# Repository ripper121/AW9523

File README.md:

# AW9523 is a 16 I/O Port-Expander
#### What is it?
AW9523 is a 16 I/O Port-Expander. Very cheap and easy to use with Arduino.

Arduino Library: [Github](https://github.com/adafruit/Adafruit_AW9523)

#### Why did you make it?
I looked for a cheap and small port Expander and found that part on LCSC, so I created this PCB.

#### What makes it special?
AW9523 Features:

- 16 multi-function I/O, each for LED drive (current-source dimming) or GPIO mode
- 256 steps linear dimming in LED drive mode
- Any GPIO can be configured as an input or an output independently
- Support interrupt, 8us deglitch, low-level active
- Standard I2C interface, A1/A0 select I2C device address
- SDA, SCL, SHDN, and all GPIO can accept in 1.8V logic input
- ESD protection: ±4000V HBM (MIL-STD-883H Method 3015.8 standard）
- Latch-up ：±450mA（ JEDEC STANDARD NO.78C SEPTEMBER 2010 standard）
- Supply shutdown function, low-level active
- 2.5V~5.5V power supply
- I2C address default 0x58 (can be 0x59, 0x5A or 0x5B)

You can buy this board form my Tindie Store: https://www.tindie.com/products/ripper121/aw9523-breakout-16-io-port-expander/

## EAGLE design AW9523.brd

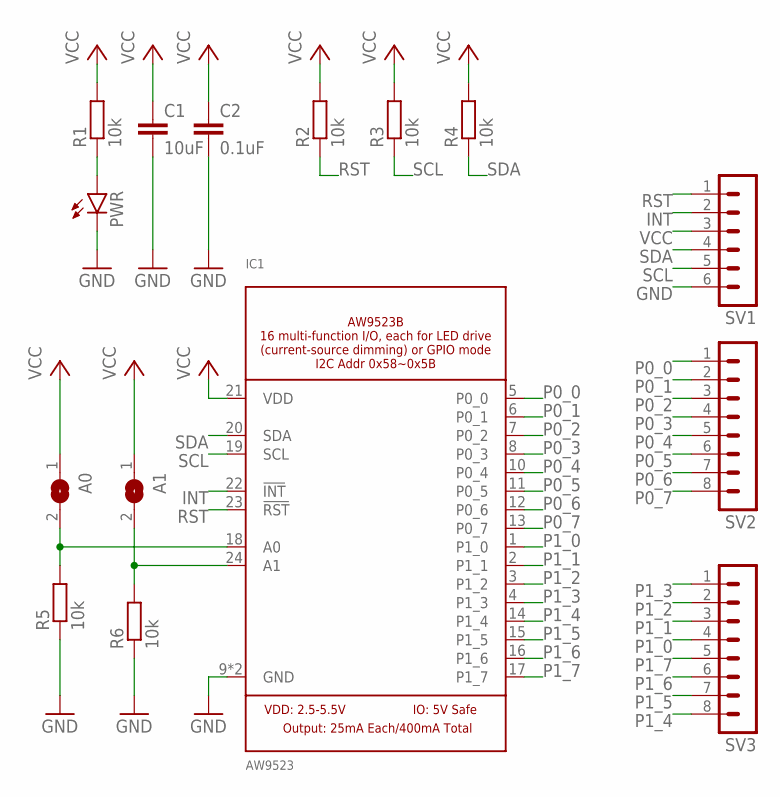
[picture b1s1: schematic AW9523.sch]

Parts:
A0, A1: SJ
C1: 10uF; C0603
C2: 0.1uF; C0603
IC1: AW9523; QFN24_4MM_SMSC
PWR: LEDCHIP-LED0603; CHIP-LED0603
R1, R2, R3, R4, R5, R6: 10k; R0603
SV1: MA06-1
SV2, SV3: MA08-1

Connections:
GND: C1.2, C2.2, IC1.9 (GND), IC1.GND, PWR.C, R5.1, R6.1, SV1.6
INT: IC1.22 (!INT), SV1.2
unnamed: A0.2, IC1.18 (A0), R5.2
unnamed: A1.2, IC1.24 (A1), R6.2
unnamed: PWR.A, R1.1
P0_0: IC1.5 (P0_0), SV2.1
P0_1: IC1.6 (P0_1), SV2.2
P0_2: IC1.7 (P0_2), SV2.3
P0_3: IC1.8 (P0_3), SV2.4
P0_4: IC1.10 (P0_4), SV2.5
P0_5: IC1.11 (P0_5), SV2.6
P0_6: IC1.12 (P0_6), SV2.7
P0_7: IC1.13 (P0_7), SV2.8
P1_0: IC1.1 (P1_0), SV3.4
P1_1: IC1.2 (P1_1), SV3.3
P1_2: IC1.3 (P1_2), SV3.2
P1_3: IC1.4 (P1_3), SV3.1
P1_4: IC1.14 (P1_4), SV3.8
P1_5: IC1.15 (P1_5), SV3.7
P1_6: IC1.16 (P1_6), SV3.6
P1_7: IC1.17 (P1_7), SV3.5
RST: IC1.23 (!RST), R2.1, SV1.1
SCL: IC1.19 (SCL), R3.1, SV1.5
SDA: IC1.20 (SDA), R4.1, SV1.4
VCC: A0.1, A1.1, C1.1, C2.1, IC1.21 (VDD), R1.2, R2.2, R3.2, R4.2, SV1.3

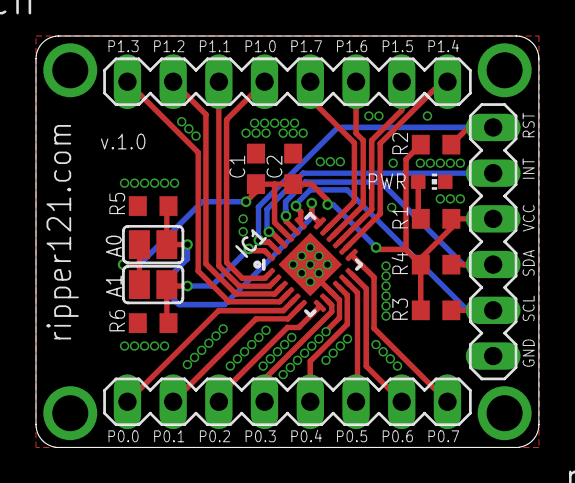
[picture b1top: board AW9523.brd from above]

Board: 2 copper layers, 27.9 x 22.9 mm, 15 parts (0 on the bottom side), 25 nets.

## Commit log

2021-02-24 first release
2021-02-24 added version label
2021-02-24 changed PWR label position, 2mm Via to GND
2021-02-24 ready for prod
2021-02-24 added pcb size
